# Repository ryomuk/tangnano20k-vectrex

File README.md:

# tangnano20k-vectrex
Tang Nano 20K top level module for Dar's Vectrex

This document is written mostly in Japanese. If necessary, please use a translation service such as DeepL (I recommend this) or Google.

## 概要
- Vectrex by Dar (darfpga@aol.fr) http://darfpga.blogspot.fr をTang Nano 20Kで動作させるためのトップレベルモジュール，オシロスコープ用信号出力のためのDAC(MCP4911)用モジュール，および周辺回路の回路図です．
- とりあえず作ってみただけなので，動作は完全ではありませんし，デバッグ用のコード等も入っています．
- [SourceForge DarFPGA](https://sourceforge.net/projects/darfpga/files/Software%20VHDL/vectrex/)にあったDE10-lite用のソースを改変して作りました．
- オリジナルのパッケージのREADME.TXTにあるように，下記のことを理解した上でご使用下さい．
  - Educational use only
  - Do not redistribute synthetized file with roms
  - Do not redistribute roms whatever the form
  - Use at your own risk

### rev0.3 (まだ改善の余地があり，改版予定ありです．)
- VGA出力用のコードと回路は削除して，XYモニター(オシロスコープ)用の出力専用にしました．
- Sony WatchmanをXYモニタに改造するための回路を追加しました．この回路についての詳細は[https://github.com/ryomuk/XYamp](https://github.com/ryomuk/XYamp)を参照して下さい．

- コントローラーをアナログ対応にしました．TangNano20kゲームキットのコントローラは粗くてスティックの稼働範囲も狭いので，SONY純正のDualShock 2(SCPH-10010)をお薦めします．
- 基板を作ってみました．ブレッドボード版のノイズが改善されるかと思ったのですが改善されませんでした．

FPGA基板

XYアンプ基板

電池ボックスに収納しようとしたけど入らない．

## コンパイル方法

1. [SourceForge DarFPGA](https://sourceforge.net/projects/darfpga/files/Software%20VHDL/vectrex/)にある vhdl_vectrex_rev_0_2_2018_06_12.zip を展開する．
2. 展開してできた下記フォルダを，vectrex_project/src/に中身ごとコピーする．
```
cp -a rtl_dar rtl_jkent rtl_mikej rtl_pace vectrex_project/src/
```
3. ROMデータのvhdlファイルを用意して，romフォルダを作成してそこに置く．
```
mkdir vectrex_project/src/rom
cp vectrex_exec_prom.vhd vectrex_project/src/rom/ (必須)
cp vectrex_scramble_prom.vhd vectrex_project/src/rom/ (ゲームROMデータの例)
```
4. Gowin EDAでプロジェクト vectrex_project.gprj を開いてビルドする．
- "Project->Configuration->Dual-Purpose Pin->Use SSPI as regular IO"をチェックして下さい
- ROMデータのファイルは，プロジェクトに適宜追加・削除して下さい．

## ROMデータについて
- このレポジトリにはROMデータはありません．(romフォルダにあるのは空のテンプレートファイルです．)
- 必要なROMデータは何らかの方法で入手して，オリジナルのパッケージに含まれるREADME.TXTに従ってvhdlファイルを作成して下さい．
- データをVHDLに変換するスクリプトrom/rom2vhd.pl を使ってもいいかも．
- romの名前，サイズに応じて，rtl_dar/vectrex.vhdを適宜修正して下さい．

## その他
- このプロジェクトはあくまでFPGAを使う練習用の試みなので，バグ等があってもメンテナンスをする予定はありません．

# 動画
動作している様子です．

## その他の画像

## 更新履歴
- 2023/6/13: 初版公開
- 2023/6/13: 回路図にLPFが抜けていたので追加
- 2023/11/14: rev0.3公開．初版はold/rev0.1に移動．

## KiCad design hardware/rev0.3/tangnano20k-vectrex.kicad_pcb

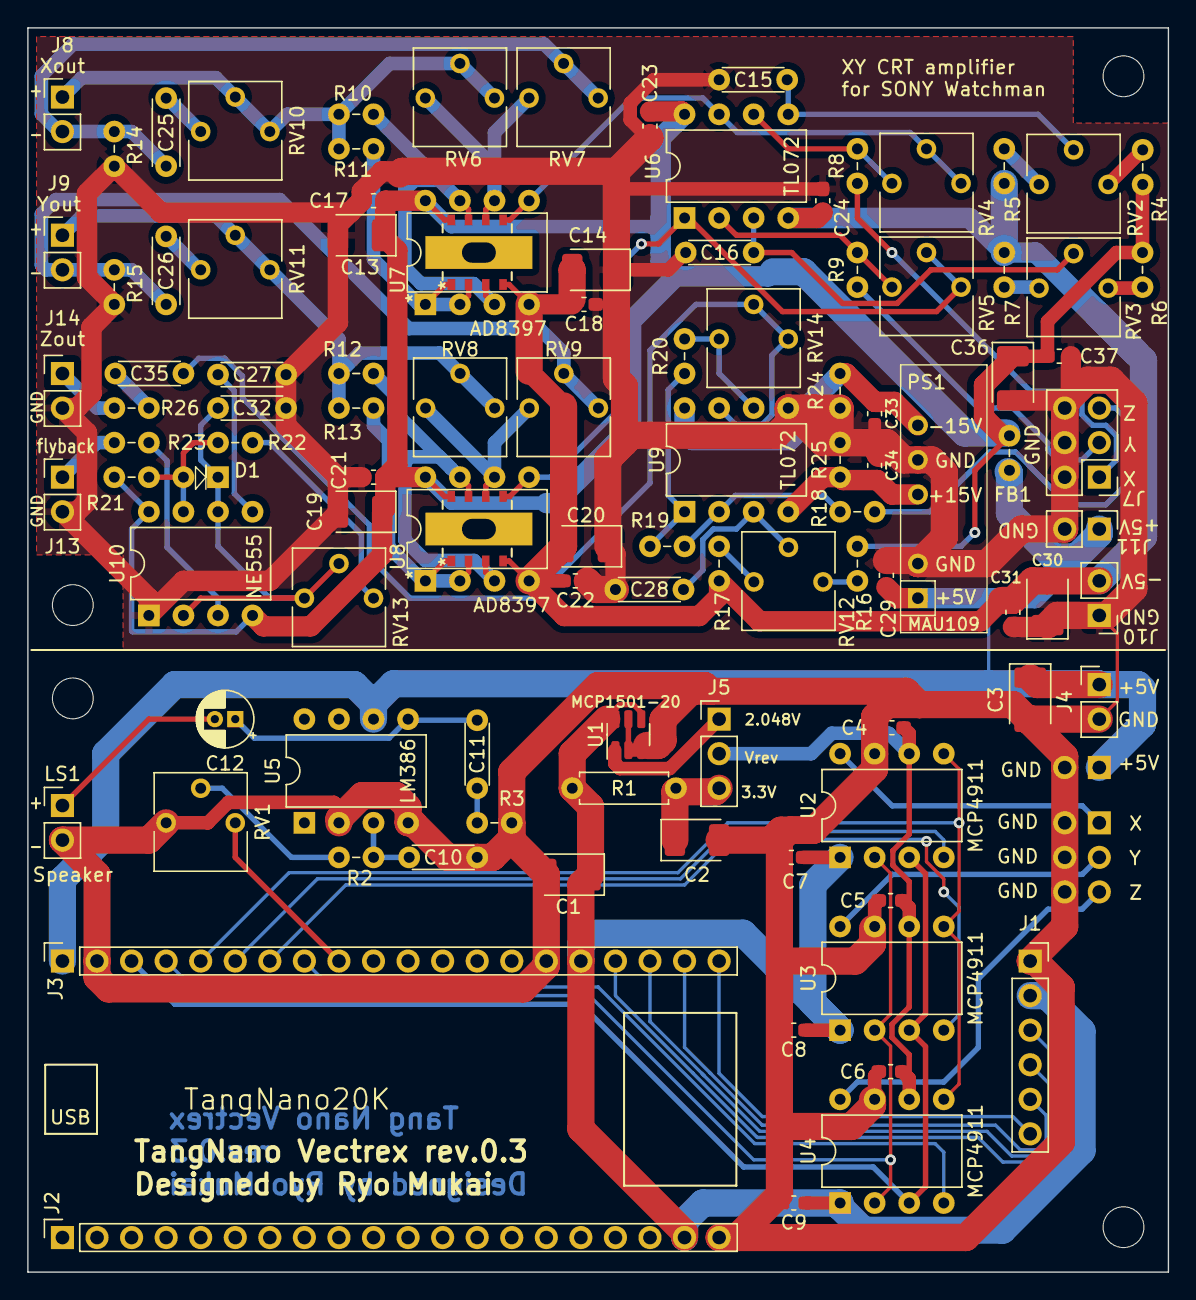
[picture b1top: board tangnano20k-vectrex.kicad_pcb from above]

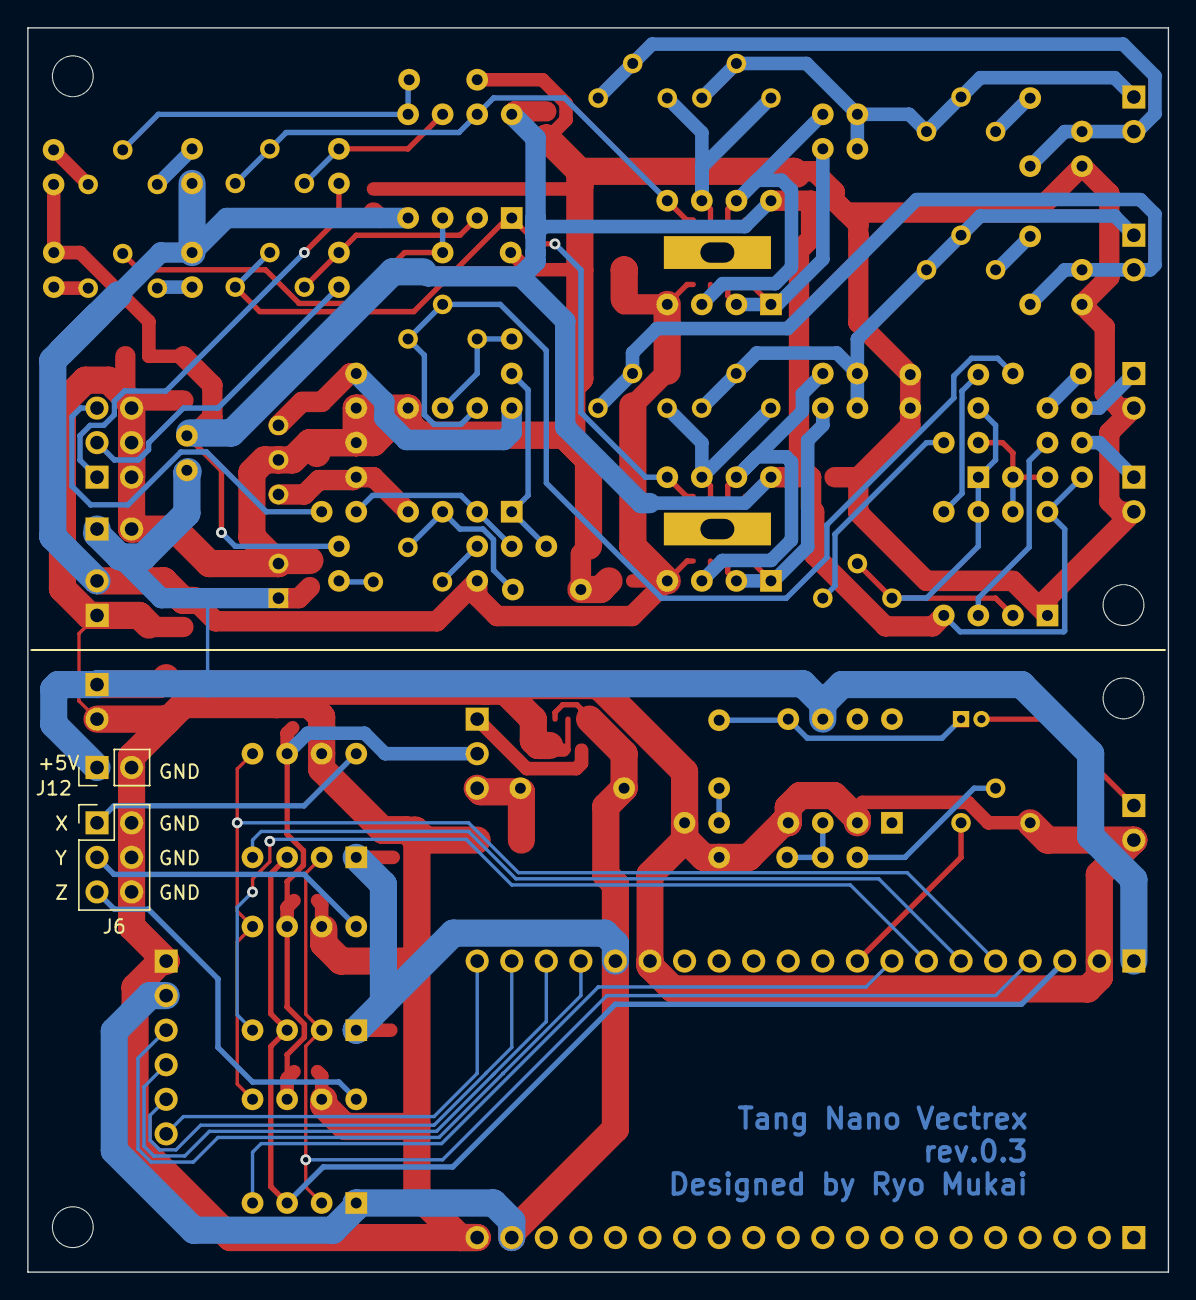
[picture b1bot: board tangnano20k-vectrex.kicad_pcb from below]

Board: 2 copper layers, 83.8 x 91.4 mm, 109 parts (2 on the bottom side), 69 nets.

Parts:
C1, C2, C3, C13, C14, C19, C20, C30, C36: 22u; CP_EIA-3528-15_AVX-H_Pad1.50x2.35mm_HandSolder
C4, C5, C6, C7, C8, C9, C17, C18, C21, C22, C23, C24, C31, C37: 0.1u; C_0603_1608Metric_Pad1.08x0.95mm_HandSolder
C10, C27: 0.01u; C_Disc_D4.3mm_W1.9mm_P5.00mm
C11: 0.047uF; C_Disc_D4.3mm_W1.9mm_P5.00mm
C12: 220u; CP_Radial_D4.0mm_P1.50mm
C15, C16, C28: 0.1u; C_Disc_D4.3mm_W1.9mm_P5.00mm
C25, C26: 1u; C_Disc_D4.7mm_W2.5mm_P5.00mm
C29: 2.2u; C_0603_1608Metric_Pad1.08x0.95mm_HandSolder
C32: 4700p; C_Disc_D4.3mm_W1.9mm_P5.00mm
C33, C34: 1u; C_0603_1608Metric_Pad1.08x0.95mm_HandSolder
C35: 0.068u; C_Disc_D4.3mm_W1.9mm_P5.00mm
D1: 1N4148; D_DO-35_SOD27_P2.54mm_Vertical_AnodeUp
FB1: FerriteBead; R_Axial_DIN0207_L6.3mm_D2.5mm_P2.54mm_Vertical
H1, H2, H3, H4: MountingHole; MountingHole_3mm
J1: Joystick; PinSocket_1x06_P2.54mm_Vertical
J2, J3: TangNano20K; PinSocket_1x20_P2.54mm_Vertical
J4, J11, J12: 5V; PinHeader_1x02_P2.54mm_Vertical
J5: Vref; PinHeader_1x03_P2.54mm_Vertical
J6, J7: Conn_02x03_Odd_Even; PinHeader_2x03_P2.54mm_Vertical
J8: Xout; PinHeader_1x02_P2.54mm_Vertical
J9: Yout; PinHeader_1x02_P2.54mm_Vertical
J10: -5V; PinHeader_1x02_P2.54mm_Vertical
J13: flyback; PinHeader_1x02_P2.54mm_Vertical
J14: Zout; PinHeader_1x02_P2.54mm_Vertical
LS1: Speaker; PinHeader_1x02_P2.54mm_Vertical
PS1: MAU109; SIP-6_without_3pin_for_DCDC_MAU
R1: 1k; R_Axial_DIN0207_L6.3mm_D2.5mm_P7.62mm_Horizontal
R2, R19, R22: 10k; R_Axial_DIN0207_L6.3mm_D2.5mm_P2.54mm_Vertical
R3: 10; R_Axial_DIN0207_L6.3mm_D2.5mm_P2.54mm_Vertical
R4, R5, R6, R7, R16, R17: 330k; R_Axial_DIN0207_L6.3mm_D2.5mm_P2.54mm_Vertical
R8, R18, R20, R23, R26: 1k; R_Axial_DIN0207_L6.3mm_D2.5mm_P2.54mm_Vertical
R9, R21: 3.3k; R_Axial_DIN0207_L6.3mm_D2.5mm_P2.54mm_Vertical
R10, R11, R12, R13, R14, R15: 4.7; R_Axial_DIN0207_L6.3mm_D2.5mm_P2.54mm_Vertical
R24, R25: 2.2k; R_Axial_DIN0207_L6.3mm_D2.5mm_P2.54mm_Vertical
RV1, RV4, RV5, RV14: 10k; Potentiometer_TOCOS_GF063
RV2, RV3, RV7, RV12: 100k; Potentiometer_TOCOS_GF063
RV6, RV8: 1M; Potentiometer_TOCOS_GF063
RV9: 1k; Potentiometer_TOCOS_GF063
RV10, RV11: 3k; Potentiometer_TOCOS_GF063
RV13: 5k; Potentiometer_TOCOS_GF063
U1: MCP1501-20; SOT-23-6
U2, U3, U4: MCP4911; DIP-8_W7.62mm
U5: LM386; DIP-8_W7.62mm
U6, U9: TL072; DIP-8_W7.62mm
U7, U8: AD8397; DIP-8_W7.62mm_with_SOP8_with_heatpadhole
U10: NE555; DIP-8_W7.62mm

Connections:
+3.3V: C1.1, C7.1, C8.1, C9.1, J1.2, J2.19, J3.16, R1.2, U1.4 (~SHDN), U1.6 (VDD), U2.1 (Vdd), U3.1 (Vdd), U4.1 (Vdd)
+5V: C3.1, C29.1, FB1.1, J3.1, J4.1, J11.1, J12.1, PS1.1 (+VIN), U5.6 (V+)
+5VA: C13.1, C17.1, C19.1, C21.1, C23.1, C36.1, C37.1, FB1.2, R4.1, R6.1, R16.1, R21.2, U6.8 (V+), U7.8 (V+), U8.8 (V+), U10.4 (R), U10.8 (VCC)
+15V: C33.1, PS1.6 (+VOUT), R24.2, U9.8 (V+)
-5VA: C14.2, C18.2, C20.2, C22.2, C24.2, C30.2, C31.2, J10.2, R5.1, R7.1, R17.1, U6.4 (V-), U7.4 (V-), U8.4 (V-)
-15V: C34.2, PS1.4 (-VOUT), R25.1, U9.4 (V-)
GND: C1.2, C2.2, C3.2, C4.2, C5.2, C6.2, C7.2, C8.2, C9.2, C10.2, C13.2, C14.1, C15.2, C16.2, C17.2, C18.1, C19.2, C20.1, C21.2, C22.1, C23.2, C24.1, C27.2, C28.2, C29.2, C30.1, C31.1, C32.2, C33.2, C34.1, C36.2, C37.2, J1.1, J2.20, J3.2, J3.15, J4.2, J6.2, J6.4, J6.6, J7.2, J7.4, J7.6, J10.1, J11.2, J12.2, J13.2, J14.2, LS1.2, PS1.2 (-VIN), PS1.5 (COM), R3.1, R14.1, R15.1, R24.1, R25.2, RV1.1, U1.2 (GND), U1.3 (GND), U1.5 (GND), U2.7 (Vss), U3.7 (Vss), U4.7 (Vss), U5.2 (-), U5.4 (GND), U9.5 (+), U10.1 (GND)
unnamed: C11.1, C12.1, U5.5
unnamed: C11.2, R3.2
unnamed: C12.2, LS1.1
unnamed: C25.1, RV10.1
unnamed: C26.1, RV11.1
unnamed: C35.1, RV14.2, RV14.3, U9.7
unnamed: C35.2, R26.1
unnamed: D1.2 (A), R21.1, R22.2, U10.7 (DIS)
unnamed: C32.1, D1.1 (K), RV13.1, RV13.2, U10.2 (TR), U10.6 (THR)
unnamed: J5.1, U1.1 (OUT)
unnamed: C2.1, J5.3, R1.1
unnamed: J8.1, R10.2, R11.2, RV6.2, RV6.3, RV10.2, RV10.3
unnamed: C25.2, J8.2, R14.2, RV7.2, RV7.3
unnamed: J9.1, R12.2, R13.2, RV8.2, RV8.3, RV11.2, RV11.3
unnamed: C26.2, J9.2, R15.2, RV9.2, RV9.3
unnamed: J13.1, R23.2
unnamed: J14.1, R26.2
unnamed: R2.1, RV1.2
unnamed: R4.2, RV2.3
unnamed: R5.2, RV2.1
unnamed: R6.2, RV3.3
unnamed: R7.2, RV3.1
unnamed: R16.2, RV12.3
unnamed: R17.2, RV12.1
unnamed: R19.2, R20.1, U9.1
unnamed: R22.1, RV13.3
unnamed: C10.1, R2.2, U5.3 (+)
unnamed: C16.1, RV3.2, U6.3 (+)
unnamed: R9.2, RV5.1, U6.2 (-)
unnamed: C15.1, RV2.2, U6.5 (+)
unnamed: R8.2, RV4.1, U6.6 (-)
unnamed: R10.1, U7.3 (+), U7.7
unnamed: R11.1, U7.1, U7.2 (-)
unnamed: RV4.2, RV4.3, U6.7, U7.5 (+)
unnamed: RV6.1, RV7.1, U7.6 (-)
unnamed: R12.1, U8.3 (+), U8.7
unnamed: R13.1, U8.1, U8.2 (-)
unnamed: RV5.2, RV5.3, U6.1, U8.5 (+)
unnamed: RV8.1, RV9.1, U8.6 (-)
unnamed: C28.1, RV12.2, U9.3 (+)
unnamed: R18.2, R19.1, U9.2 (-)
unnamed: R20.2, RV14.1, U9.6 (-)
unnamed: C27.1, U10.5 (CV)
unnamed: R23.1, U10.3 (Q)
Vref: C4.1, C5.1, C6.1, J5.2, U2.6 (Vref), U3.6 (Vref), U4.6 (Vref)
audio_pwm: J3.9, RV1.3
beam_x: J6.1, U2.8 (Vout)
beam_x0: J7.1, R8.1
beam_y: J6.3, U3.8 (Vout)
beam_y0: J7.3, R9.1
beam_z: J6.5, U4.8 (Vout)
beam_z0: J7.5, R18.1
dac_clk: J3.3, U2.3 (SCK), U3.3 (SCK), U4.3 (SCK)
dac_cs_n: J3.4, U2.2 (~CS), U3.2 (~CS), U4.2 (~CS)
dac_ld_n: J3.5, U2.5 (~LDAC), U3.5 (~LDAC), U4.5 (~LDAC)
dac_sd0: J3.6, U2.4 (SDI)
dac_sd1: J3.7, U3.4 (SDI)
dac_sd2: J3.8, U4.4 (SDI)
joystick_clk2: J1.6, J3.20
joystick_cs2: J1.3, J3.17
joystick_miso2: J1.4, J3.18
joystick_mosi2: J1.5, J3.19

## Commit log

2023-06-13 LPF added in schematics
2023-11-14 updated to rev0.3
2023-11-14 README updated
